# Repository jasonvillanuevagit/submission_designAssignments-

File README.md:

Student Name: Jason Villanueva

Student ID: 2001255420

Student Email: villaj21@unlv.nevada.edu

Student YouTube: https://www.youtube.com/channel/UCWhx_dCVsSiSHuy-BTA8t_A

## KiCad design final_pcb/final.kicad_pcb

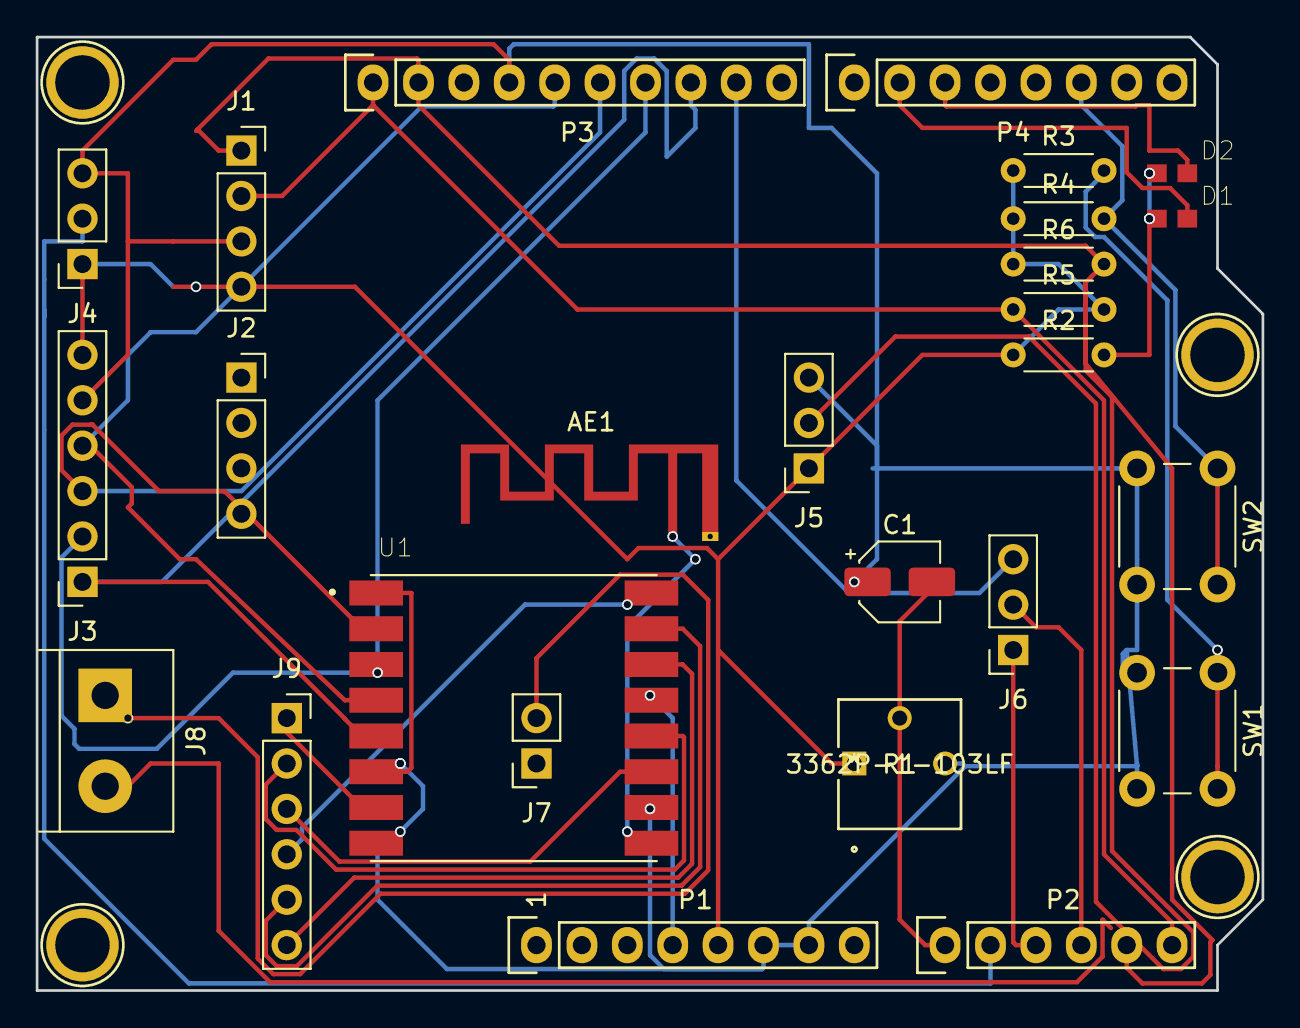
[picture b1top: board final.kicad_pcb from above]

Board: 2 copper layers, 68.6 x 53.3 mm, 30 parts (0 on the bottom side), 28 nets.

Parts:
AE1: Antenna; Texas_SWRA117D_2.4GHz_Left
C1: 100nF; CP_Elec_4x3
D1, D2: LTST-C193TBKT-5A; 0603
J1, J2: Conn_01x04_Female; PinSocket_1x04_P2.54mm_Vertical
J3, J9: Conn_01x06_Female; PinSocket_1x06_P2.54mm_Vertical
J4, J5, J6: Conn_01x03_Female; PinSocket_1x03_P2.54mm_Vertical
J7: Conn_01x02_Female; PinSocket_1x02_P2.54mm_Vertical
J8: Screw_Terminal_01x02; TerminalBlock_bornier-2_P5.08mm
P1: Power; Socket_Strip_Arduino_1x08
P2: Analog; Socket_Strip_Arduino_1x06
P3: Digital; Socket_Strip_Arduino_1x10
P4: Digital; Socket_Strip_Arduino_1x08
P5, P6, P7, P8: CONN_01X01; Arduino_1pin
R1: 3362P-1-103LF
R2, R3, R4, R5, R6: R; R_Axial_DIN0204_L3.6mm_D1.6mm_P5.08mm_Horizontal
SW1, SW2: SW_Push; SW_PUSH_6mm
U1: RFM95W-915S2; XCVR_RFM95W-915S2

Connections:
+3V3: P1.4, U1.13
+5V: J1.4, J3.6, J4.1, J5.1, P1.5, R1.1, R2.1, R3.1, R4.1, R5.2, R6.1
/2: P4.6, R4.2, SW2.1
/5(**): D2.2, P4.3
/6(**): D1.2, P4.2
/9(**): J6.3, P3.9
/10(**/SS): J3.1, P3.8, U1.5
/11(**/MOSI): J3.2, P3.7, U1.3
/12(MISO): J3.3, P3.6, U1.2
/13(SCK): J3.4, P3.5, U1.4
/A0: C1.2, P2.1, R1.2
/A1: J4.2, P2.2
/A2: J6.1, P2.3
/A3: J6.2, P2.4
/A4(SDA): J1.1, J5.2, P2.5, P3.2, R6.2
/A5(SCL): J1.2, P2.6, P3.1, R5.1
GND: C1.1, J1.3, J3.5, J4.3, J5.3, P1.6, P1.7, P3.4, R1.3, SW1.2, SW2.2, U1.1, U1.6, U1.8, U1.10
unnamed: AE1.1, U1.9
unnamed: D1.1, D2.1, R2.2
unnamed: J7.1, J8.2
unnamed: J7.2, J8.1
unnamed: J9.1, U1.7
unnamed: J9.2, U1.12
unnamed: J9.3, U1.11
unnamed: J9.4, U1.16
unnamed: J9.5, U1.15
unnamed: J9.6, U1.14
unnamed: R3.2, SW1.1

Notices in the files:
parts and their libraries:
Copyright 2016 Accelerated Designs. All rights reserved.
